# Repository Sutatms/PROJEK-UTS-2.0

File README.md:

# PROJEK-UTS-2.0
projek uts sistem embedded

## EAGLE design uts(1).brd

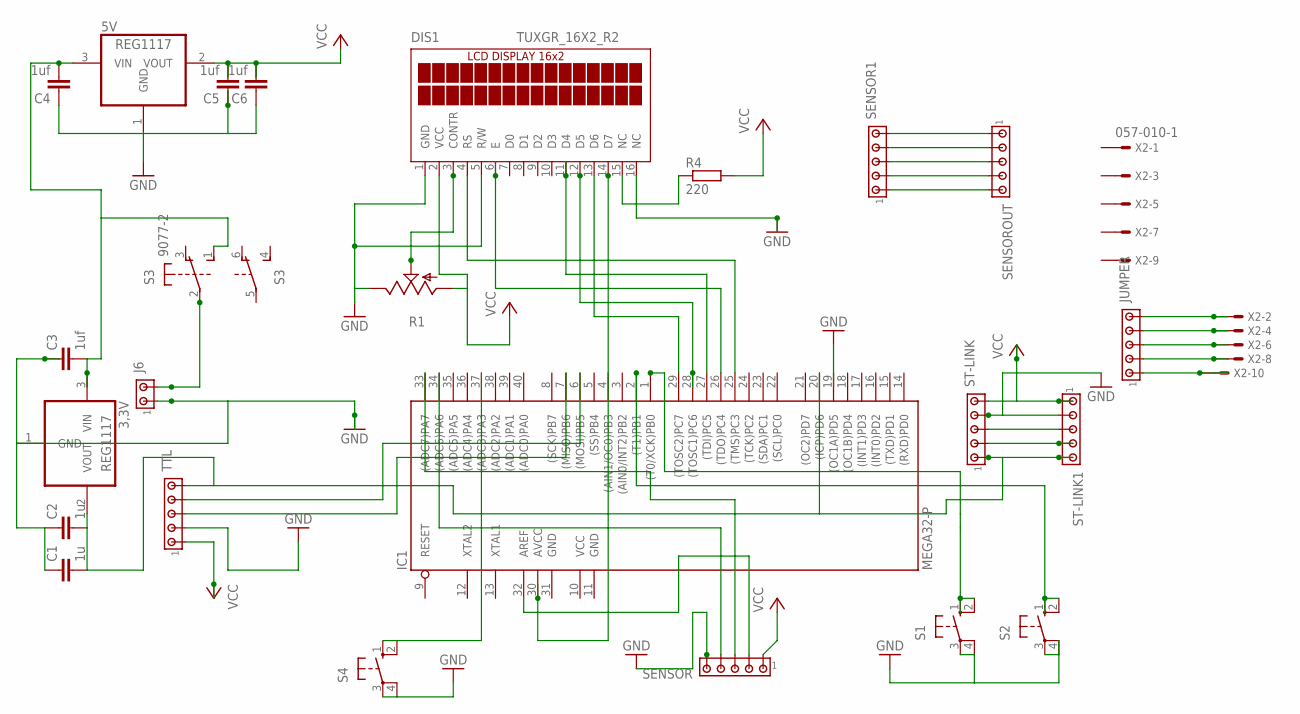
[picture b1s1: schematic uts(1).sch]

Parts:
3,3V, 5V: REG1117; SOT223
C1, C2: 1u; C0805
C3, C4, C5, C6: 1uf; C0805
DIS1: TUXGR_16X2_R2
IC1: MEGA32-P; DIL40
J6: MTA02-100; 10X02MTA
JUMPER: MTA05-100; 10X05MTA
R1: TRIM_US-CA6V; CA6V
R4: 220; M1206
S1, S2, S4: 40-XX; B3F-40XX
S3: 9077-2
SENSOR, SENSOR1: MTA05-100; 10X05MTA
SENSOROUT: MTA05-100; 10X05MTA
ST-LINK, ST-LINK1: MTA05-100; 10X05MTA
TTL: MTA05-100; 10X05MTA
X2: 057-010-1

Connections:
5V: J6.2, S3.2
GND: 3,3V.1 (GND), 5V.1 (GND), C1.1, C2.1, C3.1, C4.1, C5.1, C6.1, DIS1.1 (GND), DIS1.5 (R/W), DIS1.16 (NC), IC1.11 (GND), IC1.31 (GND), J6.1, R1.E, S1.3, S1.4 (P1), S4.3, S4.4 (P1), SENSOR.5, ST-LINK.4, ST-LINK1.2, TTL.2
unnamed: DIS1.4 (RS), IC1.25 ((TMS)PC3)
unnamed: SENSOR1.5, SENSOROUT.1
unnamed: DIS1.3 (CONTR), R1.S
unnamed: ST-LINK.2, ST-LINK1.4
unnamed: DIS1.15 (NC), R4.1
unnamed: DIS1.6 (E), IC1.26 ((TDO)PC4)
unnamed: DIS1.11 (D4), IC1.27 ((TDI)PC5)
unnamed: DIS1.12 (D5), IC1.28 ((TOSC1)PC6)
unnamed: DIS1.13 (D6), IC1.29 ((TOSC2)PC7)
unnamed: DIS1.14 (D7), IC1.30 (AVCC)
unnamed: ST-LINK.3, ST-LINK1.3
unnamed: 3,3V.3 (VIN), 5V.3 (VIN), C3.2, C4.2, S3.1 (S)
unnamed: JUMPER.5, X2.2
unnamed: JUMPER.4, X2.4
unnamed: IC1.7 ((MISO)PB6), TTL.3
unnamed: IC1.37 ((ADC3)PA3), S4.1 (S), S4.2 (S1)
unnamed: IC1.33 ((ADC7)PA7), SENSOR.3
unnamed: IC1.32 (AREF), SENSOR.2
unnamed: IC1.34 ((ADC6)PA6), SENSOR.4
unnamed: S2.3, S2.4 (P1)
unnamed: SENSOR1.4, SENSOROUT.2
unnamed: SENSOR1.3, SENSOROUT.3
unnamed: JUMPER.3, X2.6
unnamed: JUMPER.2, X2.8
unnamed: IC1.6 ((MOSI)PB5), TTL.4
unnamed: SENSOR1.2, SENSOROUT.4
unnamed: JUMPER.1, X2.10
unnamed: IC1.1 ((T0/XCK)PB0), S1.1 (S), S1.2 (S1)
unnamed: IC1.2 ((T1)PB1), S2.1 (S), S2.2 (S1)
unnamed: 3,3V.2 (VOUT), C1.2, C2.2, IC1.20 ((ICP)PD6), ST-LINK.1, ST-LINK1.5, TTL.5
unnamed: SENSOR1.1, SENSOROUT.5
VCC: 5V.2 (VOUT), C5.2, C6.2, DIS1.2 (VCC), IC1.10 (VCC), R1.A, R4.2, SENSOR.1, ST-LINK.5, ST-LINK1.1, TTL.1

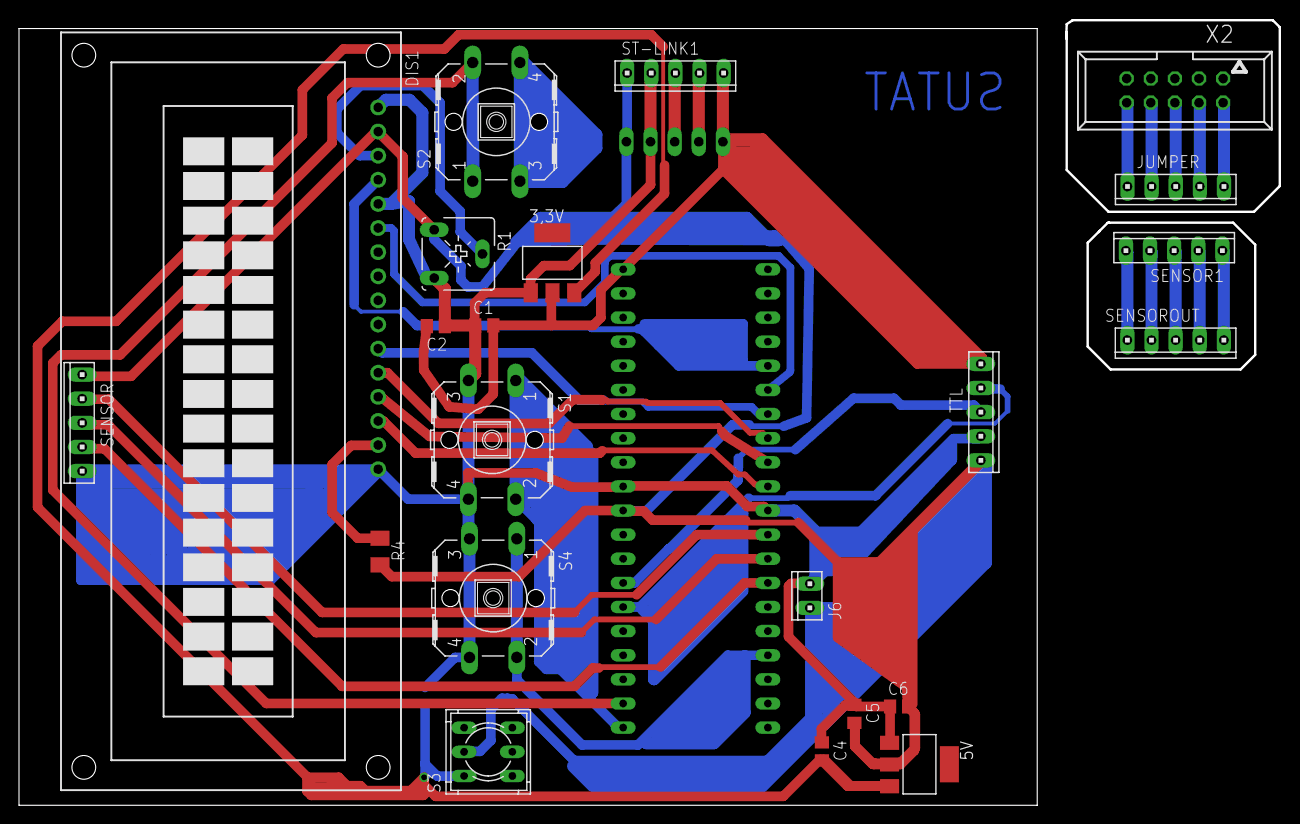
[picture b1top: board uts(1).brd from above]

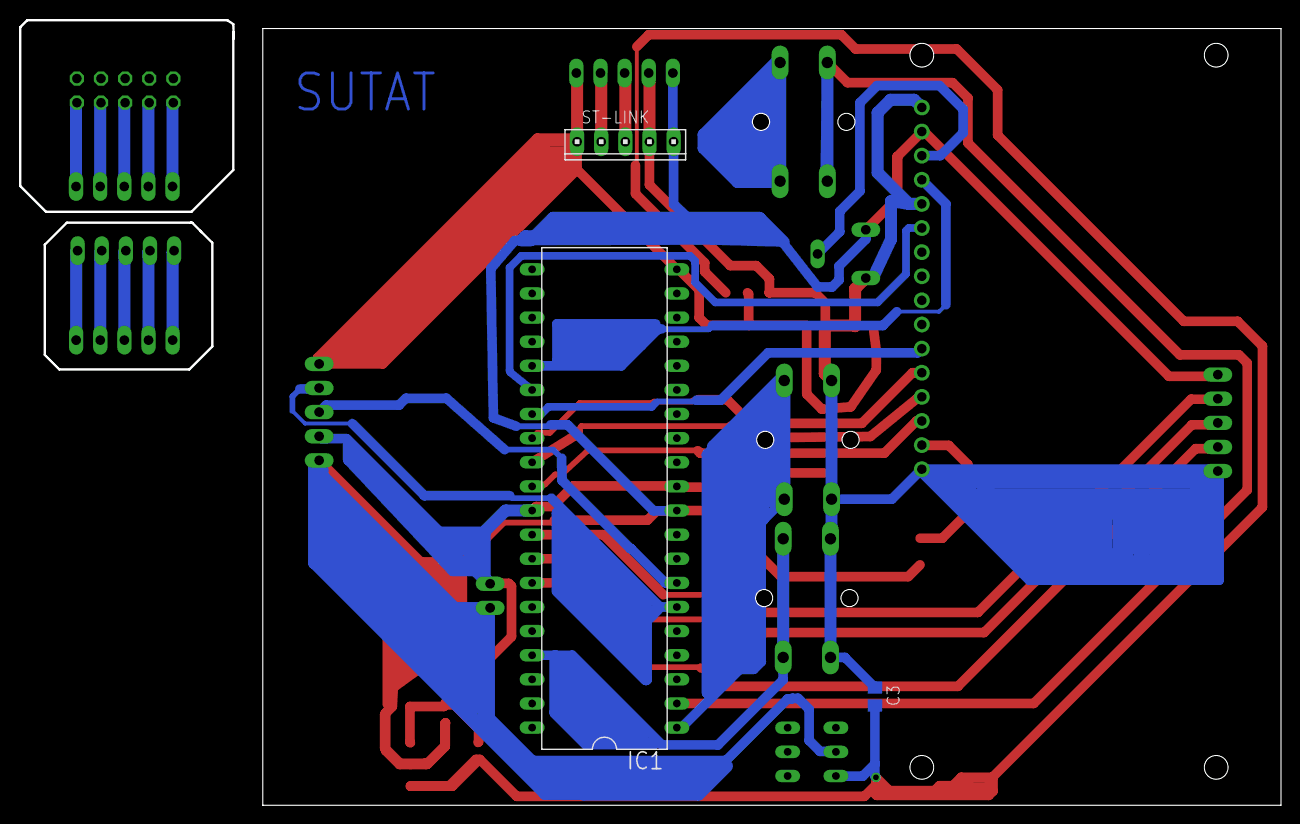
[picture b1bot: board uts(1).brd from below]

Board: 2 copper layers, 132.7 x 82.5 mm, 25 parts (3 on the bottom side), 34 nets.
